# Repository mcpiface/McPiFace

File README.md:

# McPiFace

A Simple front panel for a raspberry pi to allow for blade style rack mounting.

## Version 1.1

## Connections

McPiFace has 2 LEDs (red/green) and a push button option. These can be ignored if not required.

Should you wish to use them, the examples assume the front panel connector is wired as follows: 

Black: Pin 39 GND
Red: Pin 40 (BCM 21)
Green: Pin 38 (BCM 20)
Blue (or Yellow): Pin 37 (BCM 26)

See https://pinout.xyz/ for Raspberry Pi header pinout.

## Python Code

The Examples folder contains sample Python code to interact with the LEDs and buttons.

The McPyFace.py script can be run to monitor the Pi's temperature and change the red/green LED when it gets hot, as well as shutdown or reboot the Pi when the button is pressed.

This file should be called from rc.local at startup. Instructions are given in the file to configure this and set permissions.

## Sled

To mount the raspberry Pi a 3D printable sled is available:

https://www.thingiverse.com/thing:3488157

## Rack Mount Frame

DAP Audio 2 HE Rackblende f. Modulsystem 10 Segmente MP-1 from Music Store.

* UK: https://www.dv247.com/en_GB/GBP/DAP-Audio-2-HE-Rackblende-f-Modulsystem-10-Segmente-MP-1/art-PAH0017160-000

* Germany: https://www.musicstore.de/en_US/USD/DAP-Audio-2-HE-Rackblende-f-Modulsystem-10-Segmente-MP-1/art-PAH0017160-000

## Version History

V1.0 - had Leds "hidden" in the vent grill and no button.
V1.1 - adopted common LED/button layout used across other McPiFace front panels.

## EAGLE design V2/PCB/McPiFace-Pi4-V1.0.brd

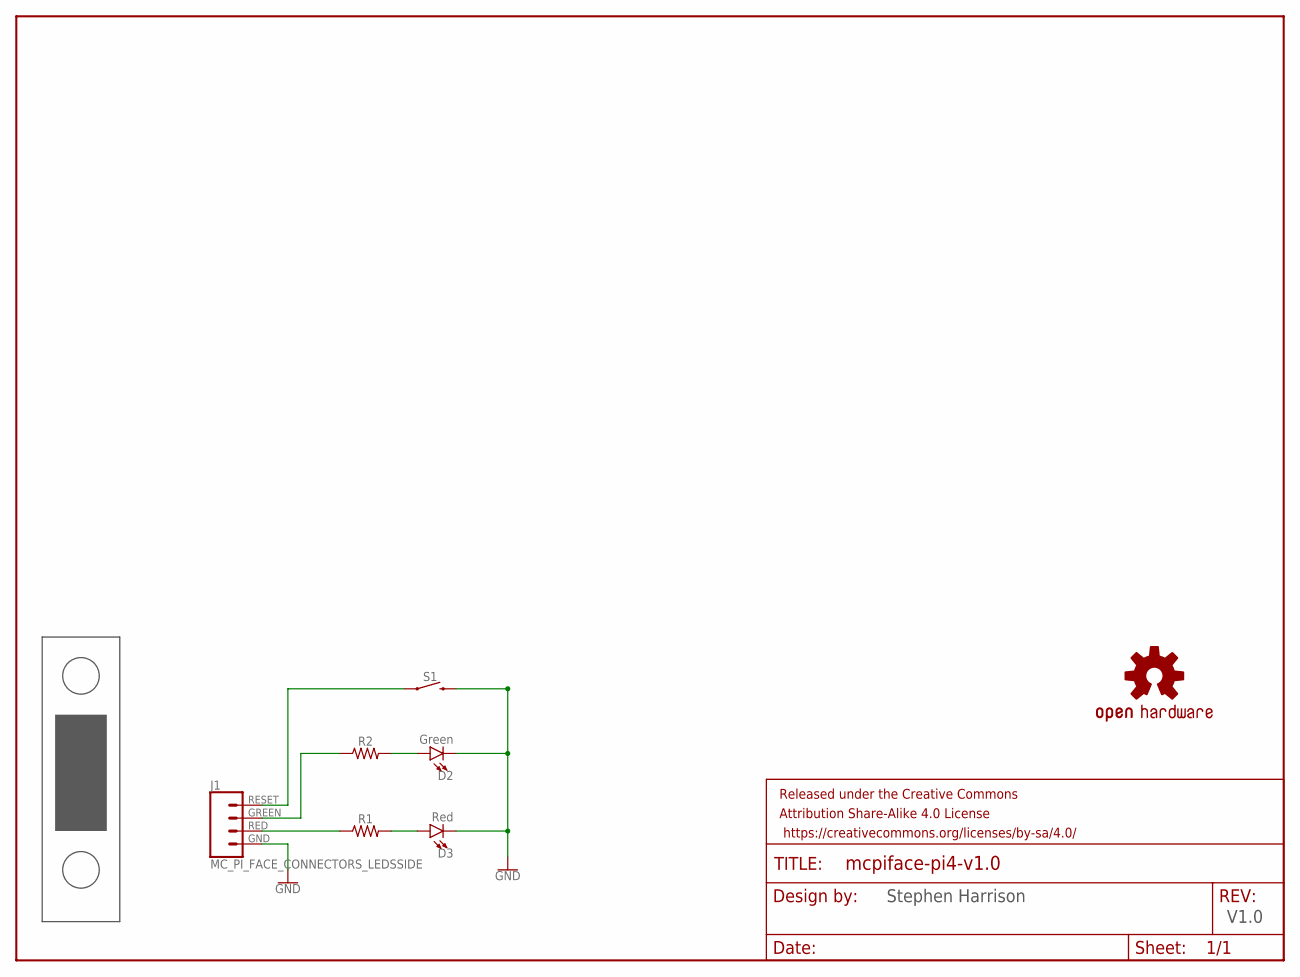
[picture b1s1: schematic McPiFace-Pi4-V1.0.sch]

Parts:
D2: Green; LED-1206-BOTTOM-2.0MM
D3: Red; LED-1206-BOTTOM-2.0MM
FRAME1: FRAME-LETTER; CREATIVE_COMMONS
J1: MC_PI_FACE_CONNECTORS_LEDSSIDE; JST-4-SH-1.0MM-SIDE
LOGO1: OSHW-LOGOL; OSHW-LOGO-L
R1, R2: 0805
S1: MOMENTARY-SWITCH-SPSTTACKTILE_SWITCH_PTH_6.0MM_NO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; TACTILE_SWITCH_PTH_6.0MM_NO_TOP_RESIST
U$1: MC_PI_4_FACE_PANEL; MC_PI_4_FACE

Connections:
GND: D2.C, D3.C, J1.GND, S1.3 (2)
unnamed: D2.A, R2.2
unnamed: D3.A, R1.2
unnamed: J1.RED, R1.1
unnamed: J1.GREEN, R2.1
unnamed: J1.RESET, S1.1

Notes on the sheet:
Stephen Harrison
V1.0

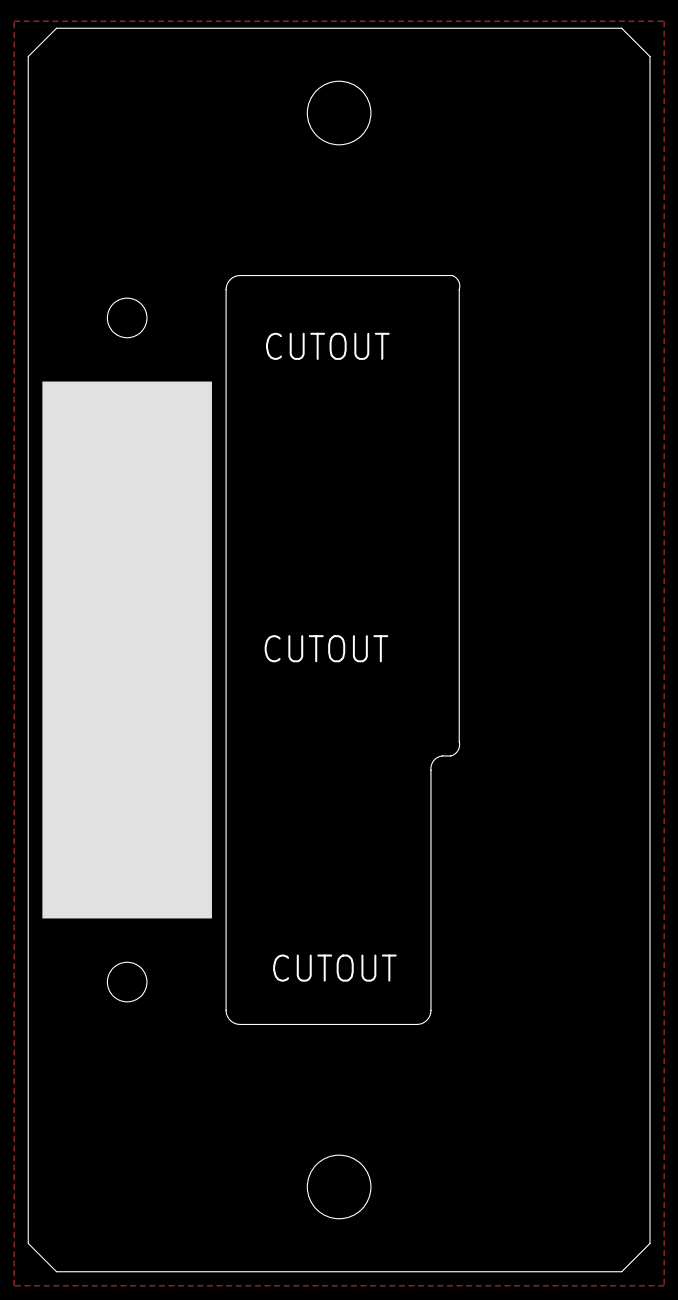
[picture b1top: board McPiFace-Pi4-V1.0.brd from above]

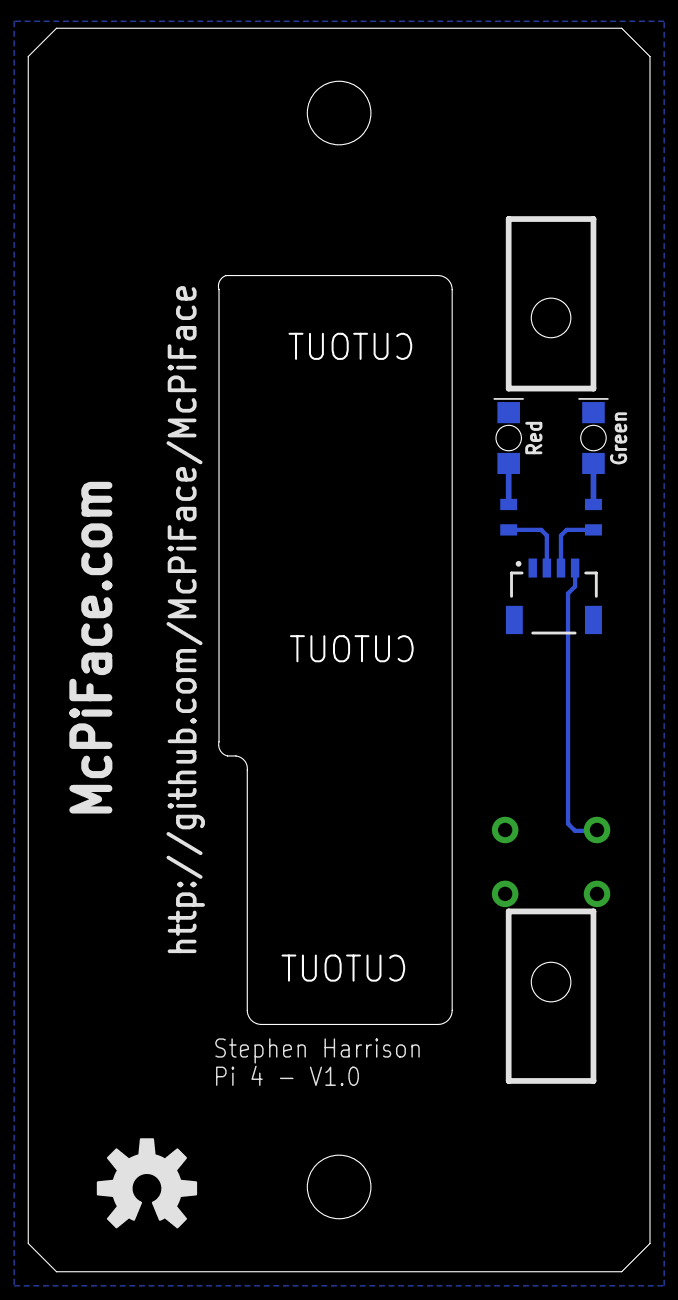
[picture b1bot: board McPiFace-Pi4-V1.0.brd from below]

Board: 2 copper layers, 44.0 x 88.0 mm, 9 parts (6 on the bottom side), 6 nets.

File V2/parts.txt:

Partlist

Exported from McPiFace-Pi4-V1.0.brd at 12/01/2020 15:57

EAGLE Version 7.4.0 Copyright (c) 1988-2015 CadSoft

Assembly variant: 

Part     Value                                                        Package                                Library            Position (mm)         Orientation

D2       Green                                                        LED-1206-BOTTOM-2.0MM                  ThingySticks       (4 59)                MR90
D3       Red                                                          LED-1206-BOTTOM-2.0MM                  ThingySticks       (10 59)               MR90
J1       MC_PI_FACE_CONNECTORS_LEDSSIDE                               JST-4-SH-1.0MM-SIDE                    McPiFace           (6.8 49.8)            MR0
R1                                                                    0805                                   SparkFun-Resistors (10 53.4)             MR90
R2                                                                    0805                                   SparkFun-Resistors (4 53.4)              MR90
S1       MOMENTARY-SWITCH-SPSTTACKTILE_SWITCH_PTH_6.0MM_NO_TOP_RESIST TACTILE_SWITCH_PTH_6.0MM_NO_TOP_RESIST ThingySticks       (7 29)                R0

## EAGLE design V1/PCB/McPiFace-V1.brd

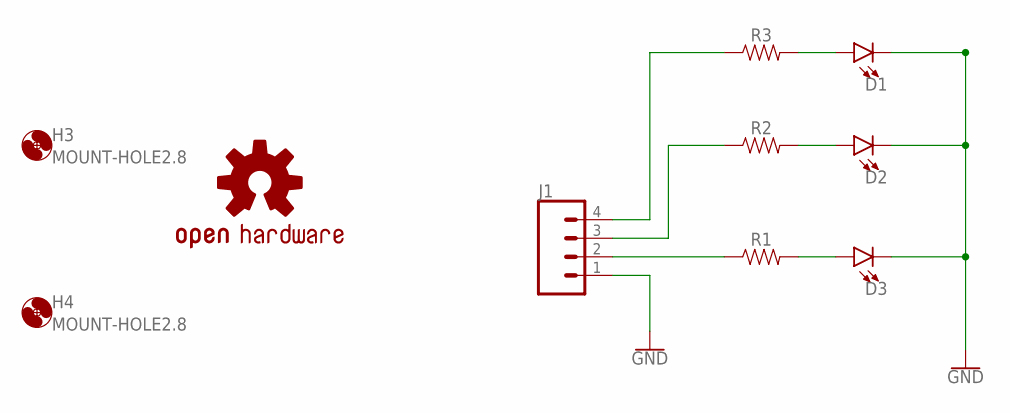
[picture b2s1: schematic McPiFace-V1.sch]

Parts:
D1, D2, D3: LED1206-BOTTOM-1.6MM; LED-1206-BOTTOM-1.6MM
H3, H4: MOUNT-HOLE2.8; 2,8
J1: CONN_04SMD2; 1X04_1MM_RA
LOGO1: OSHW-LOGOL; OSHW-LOGO-L
R1, R2, R3: 1206

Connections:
GND: D1.C, D2.C, D3.C, J1.1
unnamed: D1.A, R3.2
unnamed: D2.A, R2.2
unnamed: D3.A, R1.2
unnamed: J1.2, R1.1
unnamed: J1.3, R2.1
unnamed: J1.4, R3.1

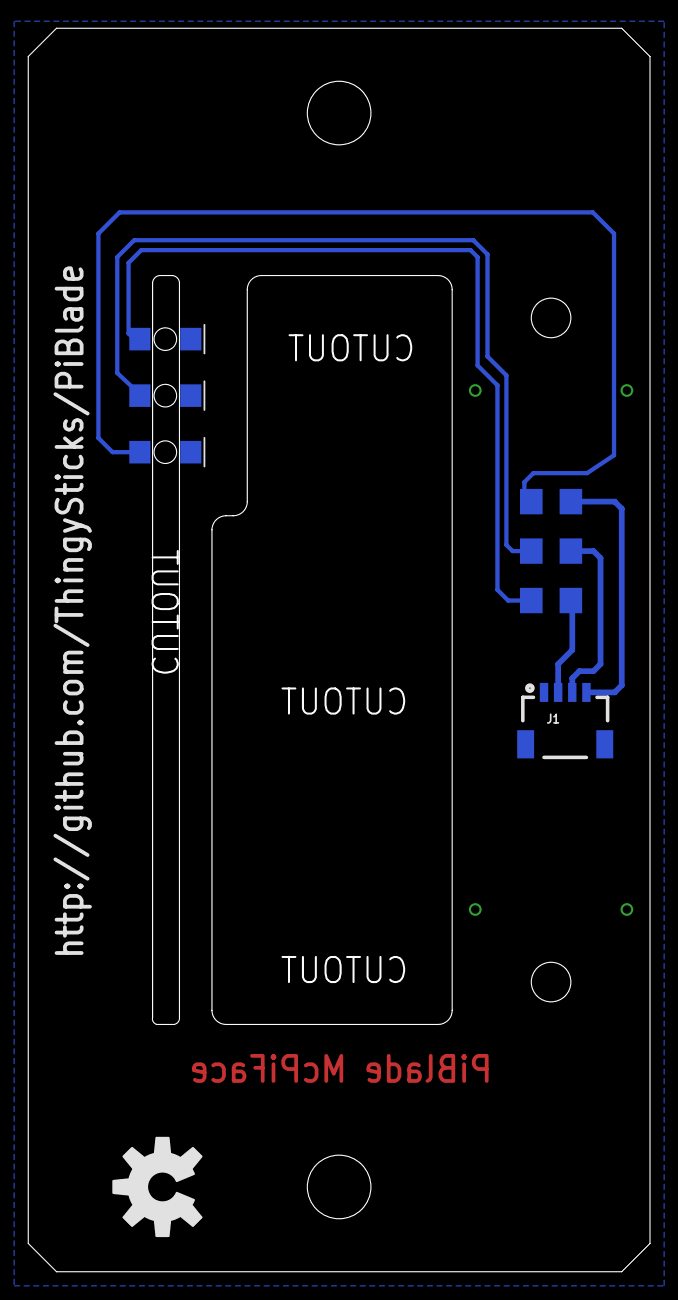
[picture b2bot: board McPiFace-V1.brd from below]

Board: 2 copper layers, 44.0 x 88.0 mm, 10 parts (8 on the bottom side), 7 nets.

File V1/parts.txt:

Partlist

Exported from McPiFace-V1.1.brd at 24/03/2019 02:59

EAGLE Version 7.4.0 Copyright (c) 1988-2015 CadSoft

Assembly variant: 

Part     Value                                                        Package                                Library            Position (mm)         Orientation

D2       Green                                                        LED-1206-BOTTOM-2.0MM                  ThingySticks       (4 59)                MR90
D3       Red                                                          LED-1206-BOTTOM-2.0MM                  ThingySticks       (10 59)               MR90
J1       MC_PI_FACE_CONNECTORS_LEDSSIDE                               JST-4-SH-1.0MM-SIDE                    McPiFace           (6.8 49.8)            MR0
R1                                                                    0805                                   SparkFun-Resistors (10 53.4)             MR90
R2                                                                    0805                                   SparkFun-Resistors (4 53.4)              MR90
S1       MOMENTARY-SWITCH-SPSTTACKTILE_SWITCH_PTH_6.0MM_NO_TOP_RESIST TACTILE_SWITCH_PTH_6.0MM_NO_TOP_RESIST ThingySticks       (7 29)                R0

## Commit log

2019-02-09 V1.1 of McPiFace front panel for Rasberry Pi.
2019-03-24 Added python script examples.
    Improved readme.
2019-03-24 Moved V1.0 images to V1.0 folder.
2019-03-24 Adding V1.1 PCB.
    Uses common layout for LEDs, removed vent hole.
2019-03-24 Improved readme.
2019-03-24 Fix for Tindie image.
2019-03-24 Added Sled and frame details.
2019-03-24 Updated wire color coding
2020-01-12 Added V2 for the Pi 4.
2020-01-12 Updated readmes.
2020-01-12 LED wiring label

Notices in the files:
README.md:
License: CC BY-SA 4.0
parts and their libraries:
SparkFun-Aesthetics: Licensing: Creative Commons ShareAlike 4.0 International - https://creativecommons.org/licenses/by-sa/4.0
SparkFun-Aesthetics: Released under the Creative Commons Attribution Share-Alike 4.0 License
SparkFun-Aesthetics: https://creativecommons.org/licenses/by-sa/4.0
